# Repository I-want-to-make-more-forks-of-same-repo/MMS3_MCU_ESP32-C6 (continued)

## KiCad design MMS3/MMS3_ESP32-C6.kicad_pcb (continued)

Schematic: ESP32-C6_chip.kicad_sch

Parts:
C17: 2.2pF; C_0402; Voltage Rated 50V; Part 0402CG2R2C500NT; LCSC C1559
C18: 3.3pF; C_0402; Voltage Rated 50V; Part 0402CG3R3C500NT; LCSC C1565
C19, C27, C29: 1uF; C_0402; Voltage Rated 25V; Tolerance ±10%; Part CL05A105KA5NQNC; LCSC C52923
C22: 1.5pF; C_0402; Voltage Rated 50V; Part 0402CG1R5C500NT; LCSC C1552
C25, C28, C37, C52, C53: 100nF; C_0402; Voltage Rated 16V; Tolerance ±10%; Part CL05B104KO5NNNC; LCSC C1525
C26: 10nF; C_0402; Voltage Rated 50V; Tolerance ±10%; Part CL05B103KB5NNNC; LCSC C15195
C57, C58: 30pF; C_0402; Voltage Rated 50V; Tolerance ±5%; Part 0402CG300J500NT; LCSC C1570
C59: 10uF; C_0402; Voltage Rated 6.3V; Tolerance ±20%; Part CL05A106MQ5NUNC; LCSC C15525
D8: TPD1E0B04DPYR; X1SON-2_L1.0-W0.6-P0.65-BI; MPN TPD1E0B04DPYR; LCSC Part C1975594
FB1: FB_0805; Current Rating 500mA; Tolerance ±25%; Part GZ2012D601TF; LCSC C1017
J5: Conn_Coaxial; SMA_Amphenol_901-143_Horizontal; LCSC Part C496551
L2: 15nH,300mA; L_0402; Tolerance ±5%; Part SDCL1005C15NJTDF; LCSC C27143
L3: 2n; L_0402; LCSC C2041629
L5: 3.9nH,300mA; L_0402; Part SDCL1005C3N9STDF; LCSC C14033
R42, R43, R44, R45, R46, R47, R48, R50, R51: 0Ω; R_0402; Overload Voltage (Max) 50V; Tolerance ±1%; Part 0402WGF0000TCE; LCSC C17168
R49: 510Ω; R_0402; Overload Voltage (Max) 50V; Tolerance ±1%; Part 0402WGF5100TCE; LCSC C25123
R52, R53, R54, R55, R56, R59, R60: 10kΩ; R_0402; Overload Voltage (Max) 50V; Tolerance ±1%; Part 0402WGF1002TCE; LCSC C25744
R57, R58: 0Ω; R_0402; Overload Voltage (Max) 50V; Tolerance ±1%; Part 0402WGF0000TCE; LCSC C17168; not fitted
SW3: TC-6615Z-12.5-260; SW-TH_4P-L7.3-TC-6615Z-12.5-260; MPN TC-6615Z-12.5-260; LCSC Part C7528758
U8: ZD25Q128CSIGT; SOP-8_L5.3-W5.3-P1.27-LS7.9-BL; MPN ZD25Q128CSIGT; LCSC Part C19626875
U11: ESP32-C6_C5364646; QFN-40_L5.0-W5.0-P0.40-TL-EP3.3; MPN ESP32-C6; LCSC Part C5364646
X2: 40MHz, 15pF; OSC-SMD_4P-L3.2-W2.5-BL_SIT8008BI; PartID X322540MPB4SI; LCSC C9010

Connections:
+3V3: C26.1, C27.1, C28.1, C29.1, C37.1, C52.1, C53.1, C59.1, FB1.2, R52.2, R53.2, R54.2, R55.1, R56.1, R59.2, R60.2, U8.8 (VCC), U11.5 (VDDPST1), U11.28 (VDDPST2), U11.37 (VDDA1), U11.40 (VDDA2); also elsewhere on the board
/ChainBus + ALtmode/Altmode1: U11.35 (SDIO_DATA2); also elsewhere on the board
/ChainBus + ALtmode/Altmode2: U11.34 (SDIO_DATA1); also elsewhere on the board
/ChainBus + ALtmode/Altmode3: U11.27 (GPIO15); also elsewhere on the board
/ChainBus + ALtmode/Altmode4: U11.23 (VDD_SPI); also elsewhere on the board
/ChainBus + ALtmode/Chainbus.CS: U11.36 (SDIO_DATA3); also elsewhere on the board
/ChainBus + ALtmode/Chainbus.MISO: U11.33 (SDIO_DATA0); also elsewhere on the board
/ChainBus + ALtmode/Chainbus.MOSI: U11.32 (SDIO_CLK); also elsewhere on the board
/ChainBus + ALtmode/Chainbus.RX: R55.2, U11.10 (MTMS); also elsewhere on the board
/ChainBus + ALtmode/Chainbus.SCK: U11.31 (SDIO_CMD); also elsewhere on the board
/ChainBus + ALtmode/Chainbus.SCL: R59.1, U11.13 (MTDO); also elsewhere on the board
/ChainBus + ALtmode/Chainbus.SDA: R60.1, U11.12 (MTCK); also elsewhere on the board
/ChainBus + ALtmode/Chainbus.TX: R56.2, U11.11 (MTDI); also elsewhere on the board
/ChainBus + ALtmode/Chainbus_addr1: U11.6 (XTAL_32K_P); also elsewhere on the board
/ChainBus + ALtmode/Chainbus_addr2: U11.7 (XTAL_32K_N); also elsewhere on the board
/ChainBus + ALtmode/Chainbus_addr3: U11.8 (GPIO2); also elsewhere on the board
/ChainBus + ALtmode/Chainbus_addr4: U11.9 (GPIO3); also elsewhere on the board
/ChainBus + ALtmode/Chainbus_addr5: U11.17 (GPIO11); also elsewhere on the board
/ChainBus + ALtmode/Chainbus_addr6: U11.16 (GPIO10); also elsewhere on the board
/ChainBus + ALtmode/Chainbus_addr7: R52.1, U11.15 (GPIO9); also elsewhere on the board
/ChainBus + ALtmode/Chainbus_addr8: R54.1, U11.14 (GPIO8); also elsewhere on the board
/ESP32-C6/ANT: C18.1, L3.1, U11.1 (ANT)
/ESP32-C6/ANT_CN: D8.2, J5.1 (In), R42.2, R58.2
/ESP32-C6/EN: C19.1, R53.1, SW3.1 (A), U11.4 (CHIP_PU); also elsewhere on the board
/ESP32-C6/ESP_CSPICLK: R48.1, U11.25 (SPICLK)
/ESP32-C6/ESP_SPICS0: R47.1, U11.20 (SPICS0)
/ESP32-C6/ESP_SPID: R46.1, U11.26 (SPID)
/ESP32-C6/ESP_SPIHD: R45.1, U11.24 (SPIHD)
/ESP32-C6/ESP_SPIQ: R44.1, U11.21 (SPIQ)
/ESP32-C6/ESP_SPIWP: R43.1, U11.22 (SPIWP)
/ESP32-C6/ESP_TX: R49.2, U11.29 (U0TXD)
/ESP32-C6/GPIO12: R51.1, U11.18 (GPIO12)
/ESP32-C6/GPIO13: R50.1, U11.19 (GPIO13)
/ESP32-C6/More_RF: C22.2, L5.1, R42.1, R57.2
/ESP32-C6/RF: C17.1, C22.1, L3.2
/ESP32-C6/SPICLK: R48.2, U8.6 (SCLK)
/ESP32-C6/SPICS0: R47.2, U8.1 (~CS)
/ESP32-C6/SPID: R46.2, U8.5 (SI(IO0))
/ESP32-C6/SPIHD: R45.2, U8.7 (~HOLD/RESET#(IO3))
/ESP32-C6/SPIQ: R44.2, U8.2 (SO(IO1))
/ESP32-C6/SPIWP: R43.2, U8.3 (WP#(IO2))
/ESP32-C6/UART0.RX: R49.1; also elsewhere on the board
/ESP32-C6/UART0.TX: U11.30 (U0RXD); also elsewhere on the board
/ESP32-C6/USB.D+: R50.2; also elsewhere on the board
/ESP32-C6/USB.D-: R51.2; also elsewhere on the board
/ESP32-C6/VCC_RF: C25.1, FB1.1, U11.2 (VDDA3P3), U11.3 (VDDA3P3)
/ESP32-C6/XTAL_N: C57.1, U11.38 (XTAL_N), X2.3 (OSC)
/ESP32-C6/XTAL_P: L2.2, U11.39 (XTAL_P)
/ESP32-C6/XTAL_P.: C58.1, L2.1, X2.1 (OSC)
GND: C17.2, C18.2, C19.2, C25.2, C26.2, C27.2, C28.2, C29.2, C37.2, C52.2, C53.2, C57.2, C58.2, C59.2, D8.1, J5.2 (Ext), L5.2, R57.1, R58.1, SW3.2 (B), SW3.3 (C), SW3.4 (D), U8.4 (VSS), U11.41 (EP), X2.2 (GND), X2.4 (GND); also elsewhere on the board

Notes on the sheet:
MTDI
Chainbus Altmode
Matching of antenna
Boot0
Chainbus Address
RF path
Should be 24nH
EN (~{RST})
USB and UART0
Matching of chip
Chainbus UART
SDIO edges
Chainbus I2C
VSWR = 1.15
assuming Z = 32 + j5
Chainbus SPI
STRAPPING PINS GPIO8, GPIO9, GPIO15, MTMS, and MTDI are strapping pins. GPIO4 GPIO5 are MTMS MTDI
UART Flip here
40MHz Oscilator
SPI memory
Strapping Pins
MTMS
Boot1

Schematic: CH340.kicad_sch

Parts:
C14, C15: 20pF; C_0402; Voltage Rated 50V; Tolerance ±5%; Part 0402CG200J500NT; LCSC C1554
C23, C54: 100nF; C_0402; Voltage Rated 16V; Tolerance ±10%; Part CL05B104KO5NNNC; LCSC C1525
Q1, Q2: MMBT3904 100-300; Q_SOT-23; Part MMBT3904(RANGE:100-300); LCSC C20526
R28, R29: 10kΩ; R_0402; Overload Voltage (Max) 50V; Tolerance ±1%; Part 0402WGF1002TCE; LCSC C25744
U13: CH340G; SOIC-16_3.9x9.9mm_P1.27mm; LCSC C14267
X3: X322512MSB4SI; CRYSTAL-SMD_4P-L3.2-W2.5-BL; Frequency Tolerance ±10ppm; Part X322512MSB4SI; LCSC C9002

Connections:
+3V3: C23.1, C54.1, U13.4 (V3), U13.16 (VCC); also elsewhere on the board
/ChainBus + ALtmode/Chainbus_addr7: Q2.3 (C); also elsewhere on the board
/ESP32-C6/EN: Q1.3 (C); also elsewhere on the board
/ESP32-C6/UART0.RX: U13.3 (RXD); also elsewhere on the board
/ESP32-C6/UART0.TX: U13.2 (TXD); also elsewhere on the board
/UART_Programmer/Prg.D+: U13.5 (UD+); also elsewhere on the board
/UART_Programmer/Prg.D-: U13.6 (UD-); also elsewhere on the board
/UART_Programmer/XI: C14.1, U13.7 (XI), X3.1 (OSC)
/UART_Programmer/XO: C15.1, U13.8 (XO), X3.3 (OSC)
/UART_Programmer/~DTR: Q2.2 (E), R28.1, U13.13 (~DTR)
/UART_Programmer/~RTS: Q1.2 (E), R29.1, U13.14 (~RTS)
GND: C14.2, C15.2, C23.2, C54.2, U13.1 (GND), X3.2 (GND), X3.4 (GND); also elsewhere on the board
unnamed: Q1.1 (B), R28.2
unnamed: Q2.1 (B), R29.2

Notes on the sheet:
EN and Boot0 sequencing

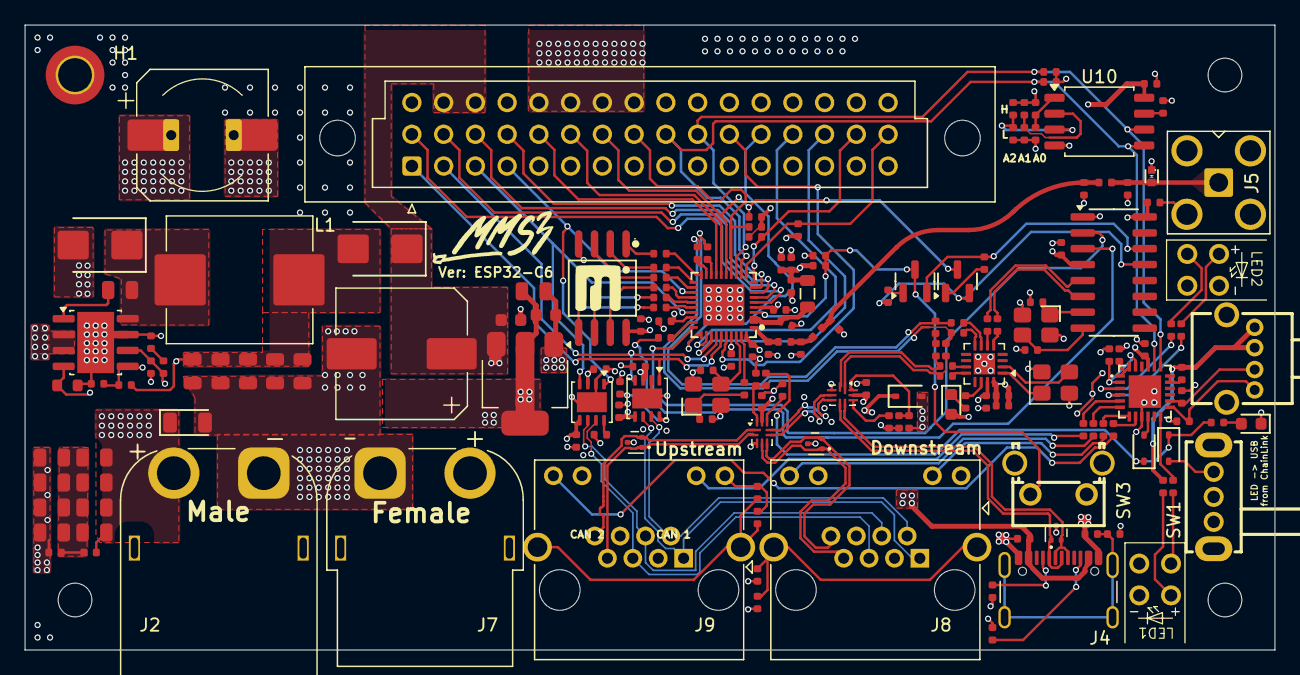
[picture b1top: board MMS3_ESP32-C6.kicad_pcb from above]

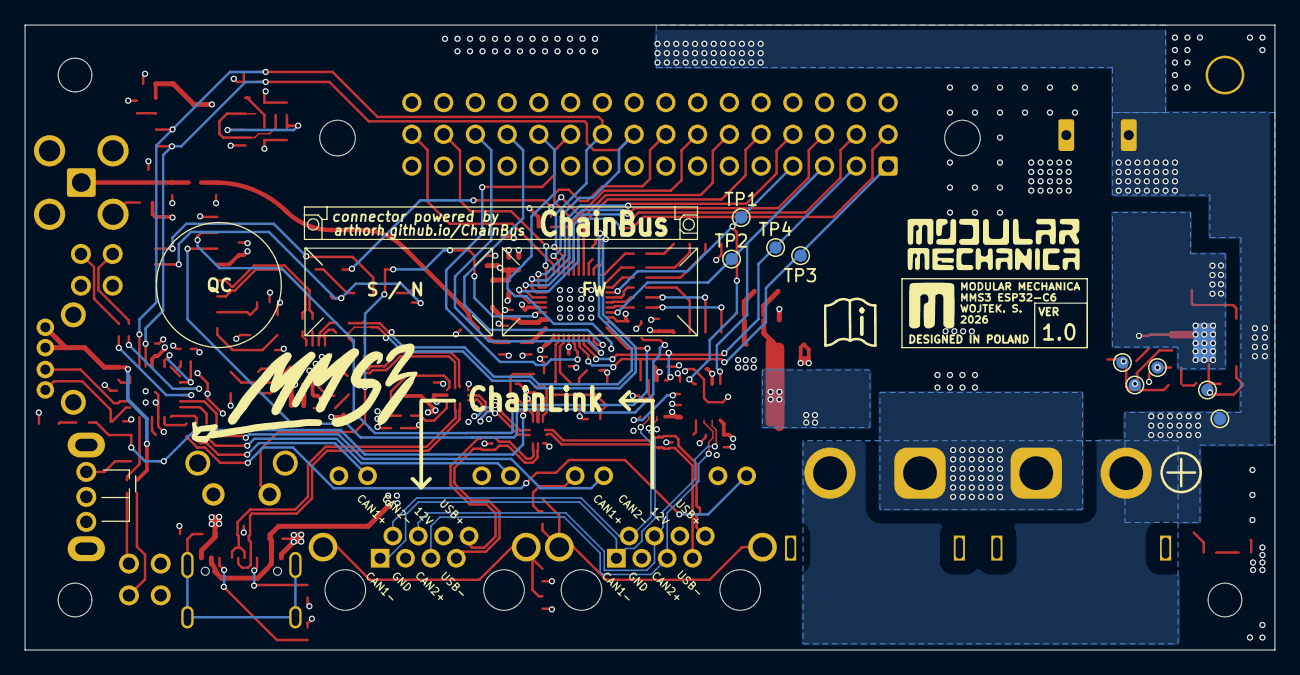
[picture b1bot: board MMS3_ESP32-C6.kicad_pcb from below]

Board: 4 copper layers, 100.0 x 50.0 mm, 185 parts (9 on the bottom side), 135 nets.

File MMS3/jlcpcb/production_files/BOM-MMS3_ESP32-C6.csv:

Comment,Designator,Footprint,LCSC,Quantity
0Ω,"R42,R43,R44,R45,R46,R47,R48,R50,R51",R_0402,C17168,9
1.5pF,C22,C_0402,C1552,1
100nF,"C10,C9",C_0603,C14663,2
100nF,"C12,C23,C25,C28,C37,C51,C52,C53,C54,C55",C_0402,C1525,10
100nF,C40,C_0805,C28233,1
100nF,"C3,C4,C5,C6,C7,C8,C900",C_0402,C307331,7
100uF,"C49,C50",CP_Elec_10x10,C249838,2
10kΩ,"R10,R12,R13,R15,R23,R24,R28,R29,R40,R41,R52,R53,R54,R55,R56,R59,R60,R61,R62,R66,R67,R68,R7,R8",R_0402,C25744,24
10nF,"C1,C13,C2,C26",C_0402,C15195,4
10uF,"C59,C902",C_0402,C15525,2
10uF,"C30,C31,C32,C33,C34,C35",C_0805,C440198,6
12kΩ,R38,R_0402,C25752,1
"15nH,300mA",L2,L_0402,C27143,1
1N5819WS,"D6,D7,D9",D_SOD-323,C191023,3
1kΩ,"R11,R30,R308,R31,R32,R35",R_0402,C11702,6
1uF,"C19,C27,C29,C904",C_0402,C52923,4
2.2pF,C17,C_0402,C1559,1
20pF,"C14,C15",C_0402,C1554,2
220nF,"C38,C39",C_0805,C5378,2
220Ω,"R1,R2,R3,R4",R_0402,C25091,4
22kΩ,"R14,R9",R_0402,C25768,2
22uF,"C41,C42,C45,C46,C47,C48",C_0805,C45783,6
22Ω,"R16,R17,R902,R903,R906,R907",R_0402,C25092,6
24.9kΩ,"R33,R34",R_0402,C25874,2
240kΩ,R39,R_0603,C4197,1
2n,L3,L_0402,C2041629,1
3.3pF,C18,C_0402,C1565,1
"3.9nH,300mA",L5,L_0402,C14033,1
30pF,"C57,C58",C_0402,C1570,2
33kΩ,"R27,R5,R6",R_0402,C25779,3
4.7nF,C44,C_0402,C1538,1
"40MHz, 15pF",X2,OSC-SMD_4P-L3.2-W2.5-BL_SIT8008BI,C9010,1
47kΩ,R21,R_0402,C25792,1
47pF,C43,C_0402,C1567,1
5.1kΩ,"R25,R26",R_0402,C25905,2
510Ω,R49,R_0402,C25123,1
8.2kΩ,R37,R_0402,C25924,1
86093488324755V1LF,J1,DIN41612_C2_3x16_Female_Vertical_THT,C5173373,1
AMASS XT60,J7,AMASS_XT60PW-F_1x02_P7.20mm_Horizontal,C428722,1
AMASS XT60,J2,AMASS_XT60PW-M_1x02_P7.20mm_Horizontal,C98732,1
AT24C256C,U10,SOIC-8_5.3x5.3mm_P1.27mm,C6482,1
CH334P,U302,QFN-16-1EP_3x3mm_P0.5mm_EP1.7x1.7mm,C5373042,1
CH340G,U13,SOIC-16_3.9x9.9mm_P1.27mm,C14267,1
Conn_Coaxial,J5,SMA_Amphenol_901-143_Horizontal,C496551,1
Crystal_GND24,Y900,Crystal_SMD_3225-4Pin_3.2x2.5mm,C9002,1
ESP32-C6_C5364646,U11,QFN-40_L5.0-W5.0-P0.40-TL-EP3.3,C5364646,1
FSUSB42UMX,"U3,U7",UQFN-10_1.4x1.8mm_P0.4mm,C11145,2
MMBT3904 100-300,"Q1,Q2",Q_SOT-23,C20526,2
Red,"D2,D301",D_0603,C2286,2
SK12D07VG5,SW1,SW-TH_SK12D07VG5-1,C431548,1
SMF58CA,D1,D_SOD-123FL,C42371753,1
SS510B,"D3,D4",D_SMB,C7420368,2
TC-6615Z-12.5-260,SW3,SW-TH_4P-L7.3-TC-6615Z-12.5-260,C7528758,1
TCA9555RTWR,U12,HVQFN-24_L4.0-W4.0-P0.50-BL-EP2.6,C42420609,1
TJA1044GTK_3Z,"U1,U6",HVSON-8-1EP_3x3mm_P0.65mm_EP1.6x2.4mm,C5215851,2
TL2243,KEY1,KEY-TH_TL2243,C273515,1
TPD1E0B04DPYR,D8,X1SON-2_L1.0-W0.6-P0.65-BI,C1975594,1
TPD2EUSB30DRTR-TP,"U4,U5,U9",SOT-723,C2844720,3
TPS54560BDDA,U2,Texas_R-PDSO-G8_EP2.95x4.9mm_Mask2.4x3.1mm_ThermalVias,C1850354,1
USB_C_Receptacle_USB2.0_16P,J4,USB_C_Receptacle_GCT_USB4105-xx-A_16P_TopMnt_Horizontal,C165948,1
X322512MSB4SI,X3,CRYSTAL-SMD_4P-L3.2-W2.5-BL,C9002,1
YSPI1050-100M,L1,L_Sunlord_MWSA1005S,C497897,1
ZD25Q128CSIGT,U8,SOP-8_L5.3-W5.3-P1.27-LS7.9-BL,C19626875,1
~,FB1,FB_0805,C1017,1
AMS1117-3.3,U15,SOT-223-3_TabPin2,,1
